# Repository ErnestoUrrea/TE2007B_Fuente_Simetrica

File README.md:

# Fuente de poder simétrica de regulación lineal
Circuito de filtrado y regulacion para una fuente de poder de 12 VDC, 0.5 A, con protección de sobrecarga e interruptor de encendido/apagado. Diseñada para la unidad de formacion **TE2007B**.<br>

**Equipo:** <br>
César Aurelio Martínez Rodríguez<br>
Mario Alberto Sánchez López<br>
Ernesto Enrique Urrea López<br>

## Especificaciones

El circuito se diseñó para cumplir con las siguientes especificaciones:
- Voltaje de salida +12 volts y -12 volts regulados
- Factor de rizo máximo antes del regulador del 6%
- Regulación de carga y de línea máxima de 10mv
- Corriente de salida máxima de 500mA
- Protección de sobrecorriente
- Interruptor 
- Led indicador
- Terminales de salida

La entrada al circuito de filtrado y regulación es proporcionada por un transformador con derivación central y salida de 30.2 Vrms.

## Diagrama esquemático

## Vista 3D

## PCB Ensamblada

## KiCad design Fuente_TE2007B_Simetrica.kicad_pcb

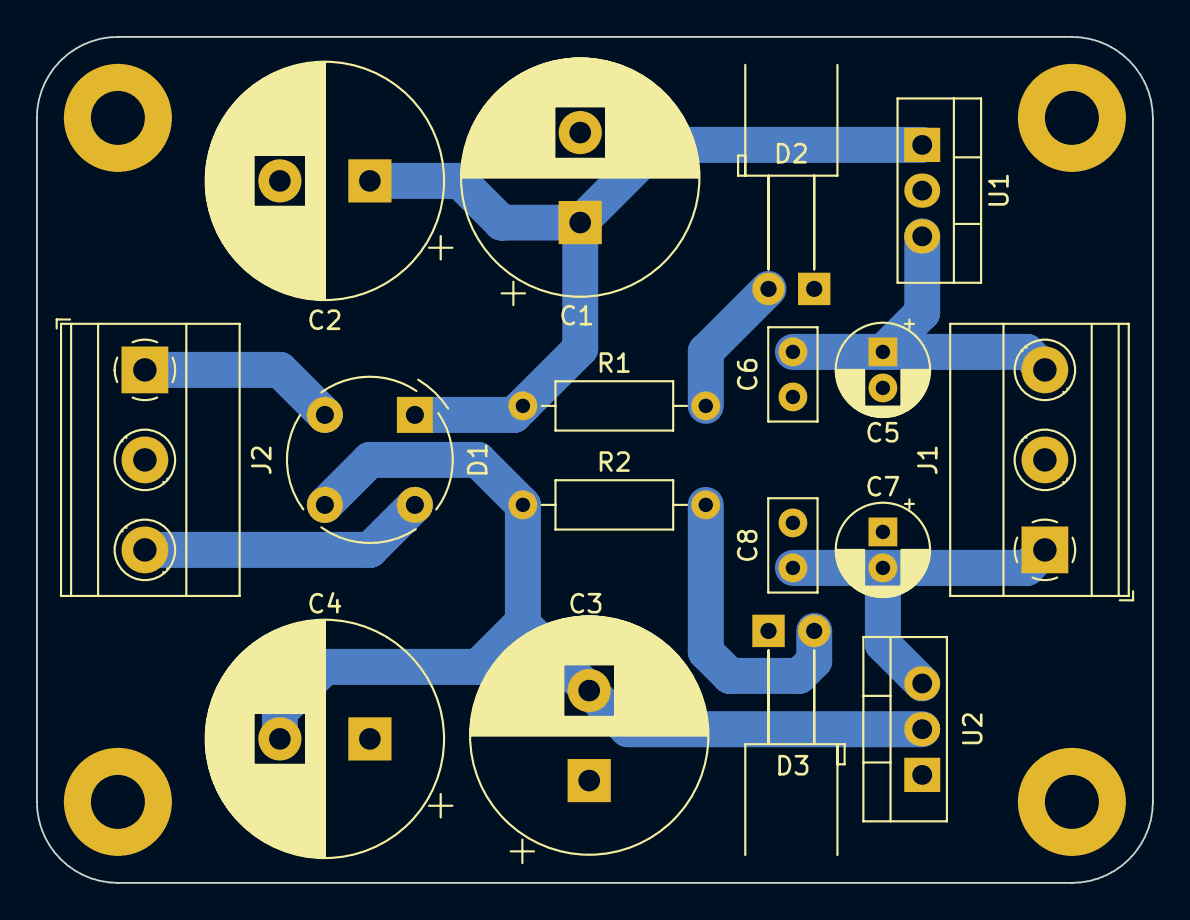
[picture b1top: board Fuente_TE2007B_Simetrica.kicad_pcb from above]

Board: 2 copper layers, 62.0 x 47.0 mm, 21 parts (0 on the bottom side), 9 nets.

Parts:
C1, C2, C3, C4: 2200 u; CP_Radial_D13.0mm_P5.00mm
C5, C7: 1 u; CP_Radial_D5.0mm_P2.00mm
C6, C8: 0.1 u; C_Disc_D5.0mm_W2.5mm_P2.50mm
D1: D_Bridge_+A-A; Diode_Bridge_Round_D9.0mm
D2, D3: LED; LED_D5.0mm_Horizontal_O6.35mm_Z3.0mm
H1, H2, H3, H4: MountingHole_Pad; MountingHole_3mm_Pad
J1, J2: Screw_Terminal_01x03; TerminalBlock_Phoenix_MKDS-1,5-3_1x03_P5.00mm_Horizontal
R1, R2: 1.1 k; R_Axial_DIN0207_L6.3mm_D2.5mm_P10.16mm_Horizontal
U1: LM7812_TO220; TO-220-3_Vertical
U2: LM7912_TO220; TO-220-3_Vertical

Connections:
GND: C1.2, C2.2, C3.1, C4.1, C5.2, C6.2, C7.1, C8.1, D2.1 (K), D3.1 (K), H1.1, H2.1, H3.1, H4.1, J1.2, J2.2, U1.2 (GND), U2.1 (GND)
NFILT: C3.2, C4.2, D1.3 (-), R2.1, U2.2 (VI)
unnamed: D2.2 (A), R1.2
unnamed: D3.2 (A), R2.2
PFILT: C1.1, C2.1, D1.1 (+), R1.1, U1.1 (VI)
VOUT+: C5.1, C6.1, J1.3, U1.3 (VO)
VOUT-: C7.2, C8.2, J1.1, U2.3 (VO)
X1: D1.2, J2.1
X3: D1.4, J2.3

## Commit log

2023-07-17 3D view image
2023-07-17 Circuit diagram image
2023-07-18 Assembled pcb image
